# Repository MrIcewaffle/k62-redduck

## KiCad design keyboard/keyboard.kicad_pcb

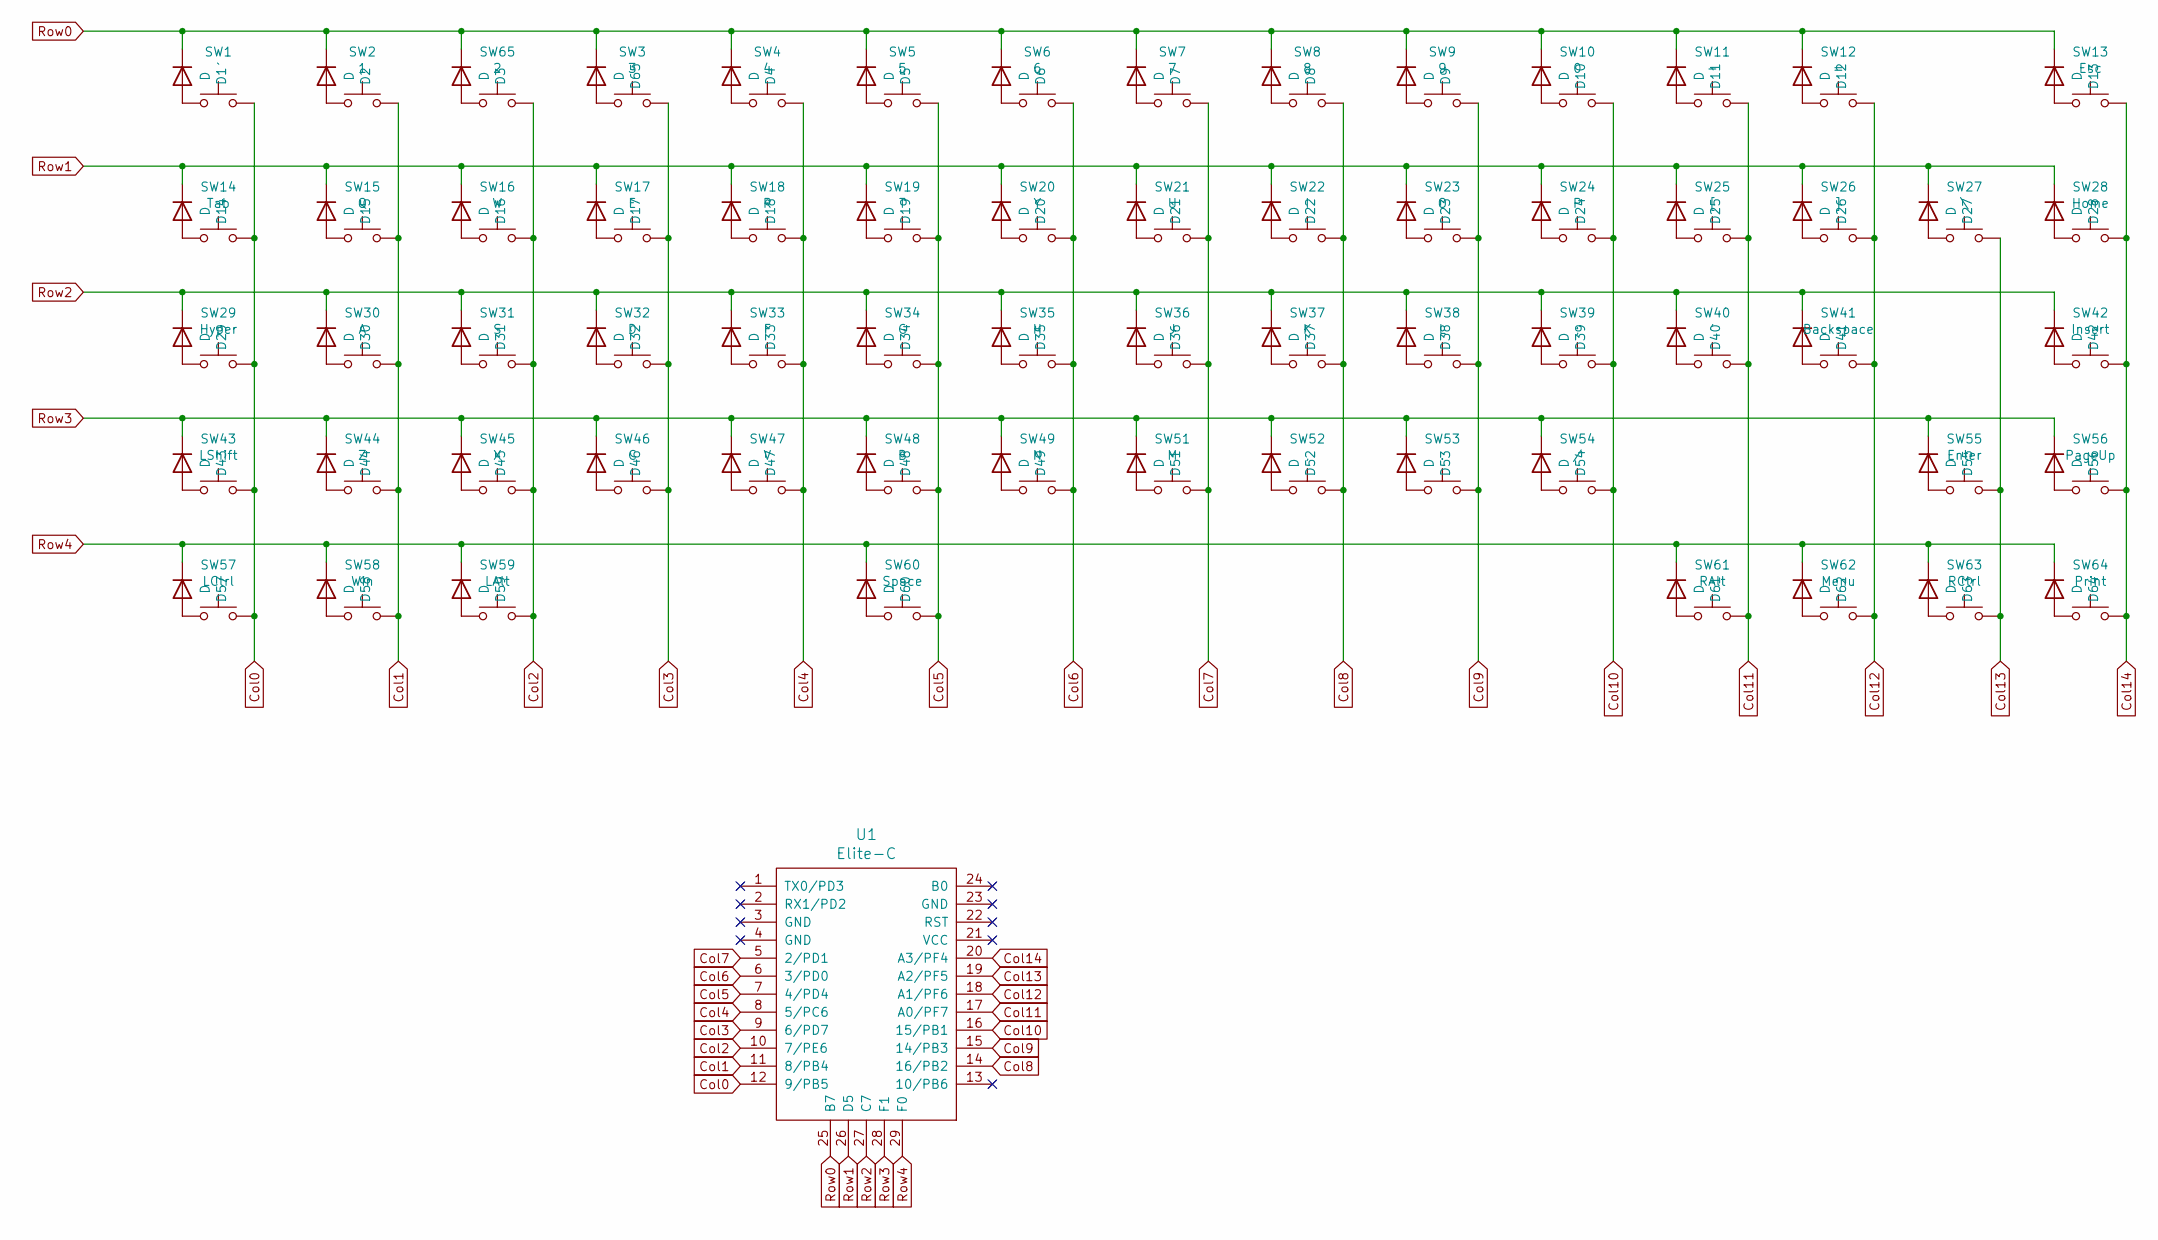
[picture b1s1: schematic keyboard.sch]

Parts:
D1, D2, D3, D4, D5, D6, D7, D8, D9, D10, D11, D12, D13, D14, D15, D16, D17, D18, D19, D20, D21, D22, D23, D24, D25, D26, D27, D28, D29, D30, D31, D32, D33, D34, D35, D36, D37, D38, D39, D40, D41, D42, D43, D44, D45, D46, D47, D48, D49, D51, D52, D53, D54, D55, D56, D57, D58, D59, D60, D61, D62, D63, D64, D65: D; D_0805
SW1: `; MX-Alps-Choc-1U-NoLED
SW2: 1; MX-Alps-Choc-1U-NoLED
SW3: 3; MX-Alps-Choc-1U-NoLED
SW4: 4; MX-Alps-Choc-1U-NoLED
SW5: 5; MX-Alps-Choc-1U-NoLED
SW6: 6; MX-Alps-Choc-1U-NoLED
SW7: 7; MX-Alps-Choc-1U-NoLED
SW8: 8; MX-Alps-Choc-1U-NoLED
SW9: 9; MX-Alps-Choc-1U-NoLED
SW10: 0; MX-Alps-Choc-1U-NoLED
SW11: -; MX-Alps-Choc-1U-NoLED
SW12: =; MX-Alps-Choc-1U-NoLED
SW13: Esc; MX-Alps-Choc-1U-NoLED
SW14: Tab; MX-Alps-Choc-1U-NoLED
SW15: Q; MX-Alps-Choc-1U-NoLED
SW16: W; MX-Alps-Choc-1U-NoLED
SW17: E; MX-Alps-Choc-1U-NoLED
SW18: R; MX-Alps-Choc-1U-NoLED
SW19: T; MX-Alps-Choc-1U-NoLED
SW20: Y; MX-Alps-Choc-1U-NoLED
SW21: U; MX-Alps-Choc-1U-NoLED
SW22: I; MX-Alps-Choc-1U-NoLED
SW23: O; MX-Alps-Choc-1U-NoLED
SW24: P; MX-Alps-Choc-1U-NoLED
SW25: [; MX-Alps-Choc-1U-NoLED
SW26: ]; MX-Alps-Choc-1U-NoLED
SW27: \\; MX-Alps-Choc-1U-NoLED
SW28: Home; MX-Alps-Choc-1U-NoLED
SW29: Hyper; MX-Alps-Choc-1U-NoLED
SW30: A; MX-Alps-Choc-1U-NoLED
SW31: S; MX-Alps-Choc-1U-NoLED
SW32: D; MX-Alps-Choc-1U-NoLED
SW33: F; MX-Alps-Choc-1U-NoLED
SW34: G; MX-Alps-Choc-1U-NoLED
SW35: H; MX-Alps-Choc-1U-NoLED
SW36: J; MX-Alps-Choc-1U-NoLED
SW37: K; MX-Alps-Choc-1U-NoLED
SW38: L; MX-Alps-Choc-1U-NoLED
SW39: ;; MX-Alps-Choc-1U-NoLED
SW40: '; MX-Alps-Choc-1U-NoLED
SW41: Backspace; MX-Alps-Choc-1U-NoLED
SW42: Insert; MX-Alps-Choc-1U-NoLED
SW43: LShift; MX-Alps-Choc-1U-NoLED
SW44: Z; MX-Alps-Choc-1U-NoLED
SW45: X; MX-Alps-Choc-1U-NoLED
SW46: C; MX-Alps-Choc-1U-NoLED
SW47: V; MX-Alps-Choc-1U-NoLED
SW48: B; MX-Alps-Choc-1U-NoLED
SW49: N; MX-Alps-Choc-1U-NoLED
SW51: M; MX-Alps-Choc-1U-NoLED
SW52: ,; MX-Alps-Choc-1U-NoLED
SW53: .; MX-Alps-Choc-1U-NoLED
SW54: /; MX-Alps-Choc-1U-NoLED
SW55: Enter; MX-Alps-Choc-1U-NoLED
SW56: PageUp; MX-Alps-Choc-1U-NoLED
SW57: LCtrl; MX-Alps-Choc-1U-NoLED
SW58: Win; MX-Alps-Choc-1U-NoLED
SW59: LAlt; MX-Alps-Choc-1U-NoLED
SW60: Space; MX-Alps-Choc-1U-NoLED
SW61: RAlt; MX-Alps-Choc-1U-NoLED
SW62: Menu; MX-Alps-Choc-1U-NoLED
SW63: RCtrl; MX-Alps-Choc-1U-NoLED
SW64: Print; MX-Alps-Choc-1U-NoLED
SW65: 2; MX-Alps-Choc-1U-NoLED
U1: Elite-C; Elite-C-castellated-29pin-holes

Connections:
Col0: SW1.2, SW14.2, SW29.2, SW43.2, SW57.2, U1.12 (9/PB5)
Col1: SW2.2, SW15.2, SW30.2, SW44.2, SW58.2, U1.11 (8/PB4)
Col2: SW16.2, SW31.2, SW45.2, SW59.2, SW65.2, U1.10 (7/PE6)
Col3: SW3.2, SW17.2, SW32.2, SW46.2, U1.9 (6/PD7)
Col4: SW4.2, SW18.2, SW33.2, SW47.2, U1.8 (5/PC6)
Col5: SW5.2, SW19.2, SW34.2, SW48.2, SW60.2, U1.7 (4/PD4)
Col6: SW6.2, SW20.2, SW35.2, SW49.2, U1.6 (3/PD0)
Col7: SW7.2, SW21.2, SW36.2, SW51.2, U1.5 (2/PD1)
Col8: SW8.2, SW22.2, SW37.2, SW52.2, U1.14 (16/PB2)
Col9: SW9.2, SW23.2, SW38.2, SW53.2, U1.15 (14/PB3)
Col10: SW10.2, SW24.2, SW39.2, SW54.2, U1.16 (15/PB1)
Col11: SW11.2, SW25.2, SW40.2, SW61.2, U1.17 (A0/PF7)
Col12: SW12.2, SW26.2, SW41.2, SW62.2, U1.18 (A1/PF6)
Col13: SW27.2, SW55.2, SW63.2, U1.19 (A2/PF5)
Col14: SW13.2, SW28.2, SW42.2, SW56.2, SW64.2, U1.20 (A3/PF4)
unnamed: D1.2 (A), SW1.1
unnamed: D2.2 (A), SW2.1
unnamed: D3.2 (A), SW65.1
unnamed: D4.2 (A), SW4.1
unnamed: D5.2 (A), SW5.1
unnamed: D6.2 (A), SW6.1
unnamed: D7.2 (A), SW7.1
unnamed: D8.2 (A), SW8.1
unnamed: D9.2 (A), SW9.1
unnamed: D10.2 (A), SW10.1
unnamed: D11.2 (A), SW11.1
unnamed: D12.2 (A), SW12.1
unnamed: D13.2 (A), SW13.1
unnamed: D14.2 (A), SW14.1
unnamed: D15.2 (A), SW15.1
unnamed: D16.2 (A), SW16.1
unnamed: D17.2 (A), SW17.1
unnamed: D18.2 (A), SW18.1
unnamed: D19.2 (A), SW19.1
unnamed: D20.2 (A), SW20.1
unnamed: D21.2 (A), SW21.1
unnamed: D22.2 (A), SW22.1
unnamed: D23.2 (A), SW23.1
unnamed: D24.2 (A), SW24.1
unnamed: D25.2 (A), SW25.1
unnamed: D26.2 (A), SW26.1
unnamed: D27.2 (A), SW27.1
unnamed: D28.2 (A), SW28.1
unnamed: D29.2 (A), SW29.1
unnamed: D30.2 (A), SW30.1
unnamed: D31.2 (A), SW31.1
unnamed: D32.2 (A), SW32.1
unnamed: D33.2 (A), SW33.1
unnamed: D34.2 (A), SW34.1
unnamed: D35.2 (A), SW35.1
unnamed: D36.2 (A), SW36.1
unnamed: D37.2 (A), SW37.1
unnamed: D38.2 (A), SW38.1
unnamed: D39.2 (A), SW39.1
unnamed: D40.2 (A), SW40.1
unnamed: D41.2 (A), SW41.1
unnamed: D42.2 (A), SW42.1
unnamed: D43.2 (A), SW43.1
unnamed: D44.2 (A), SW44.1
unnamed: D45.2 (A), SW45.1
unnamed: D46.2 (A), SW46.1
unnamed: D47.2 (A), SW47.1
unnamed: D48.2 (A), SW48.1
unnamed: D49.2 (A), SW49.1
unnamed: D51.2 (A), SW51.1
unnamed: D52.2 (A), SW52.1
unnamed: D53.2 (A), SW53.1
unnamed: D54.2 (A), SW54.1
unnamed: D55.2 (A), SW55.1
unnamed: D56.2 (A), SW56.1
unnamed: D57.2 (A), SW57.1
unnamed: D58.2 (A), SW58.1
unnamed: D59.2 (A), SW59.1
unnamed: D60.2 (A), SW60.1
unnamed: D61.2 (A), SW61.1
unnamed: D62.2 (A), SW62.1
unnamed: D63.2 (A), SW63.1
unnamed: D64.2 (A), SW64.1
unnamed: D65.2 (A), SW3.1
Row0: D1.1 (K), D2.1 (K), D3.1 (K), D4.1 (K), D5.1 (K), D6.1 (K), D7.1 (K), D8.1 (K), D9.1 (K), D10.1 (K), D11.1 (K), D12.1 (K), D13.1 (K), D65.1 (K), U1.25 (B7)
Row1: D14.1 (K), D15.1 (K), D16.1 (K), D17.1 (K), D18.1 (K), D19.1 (K), D20.1 (K), D21.1 (K), D22.1 (K), D23.1 (K), D24.1 (K), D25.1 (K), D26.1 (K), D27.1 (K), D28.1 (K), U1.26 (D5)
Row2: D29.1 (K), D30.1 (K), D31.1 (K), D32.1 (K), D33.1 (K), D34.1 (K), D35.1 (K), D36.1 (K), D37.1 (K), D38.1 (K), D39.1 (K), D40.1 (K), D41.1 (K), D42.1 (K), U1.27 (C7)
Row3: D43.1 (K), D44.1 (K), D45.1 (K), D46.1 (K), D47.1 (K), D48.1 (K), D49.1 (K), D51.1 (K), D52.1 (K), D53.1 (K), D54.1 (K), D55.1 (K), D56.1 (K), U1.28 (F1)
Row4: D57.1 (K), D58.1 (K), D59.1 (K), D60.1 (K), D61.1 (K), D62.1 (K), D63.1 (K), D64.1 (K), U1.29 (F0)

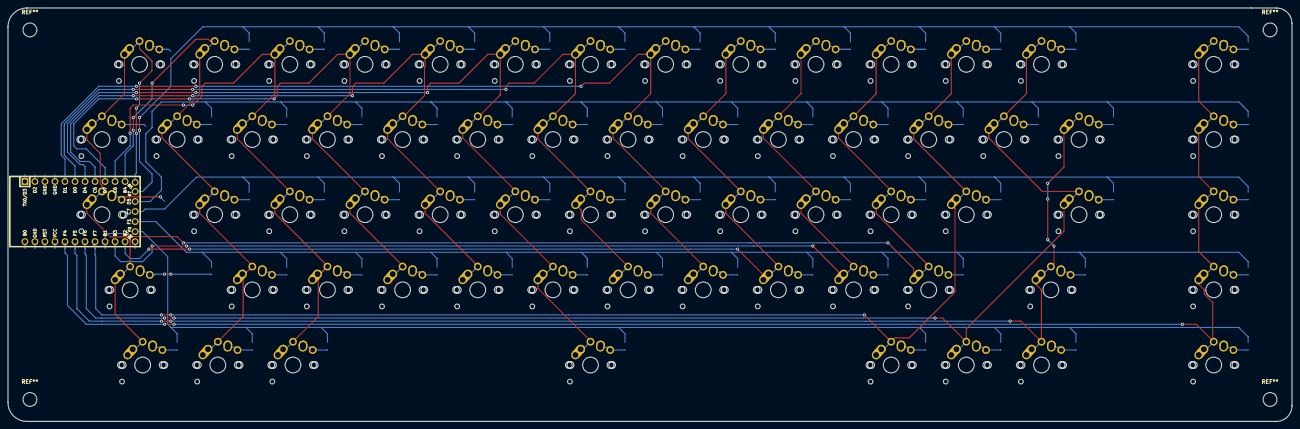
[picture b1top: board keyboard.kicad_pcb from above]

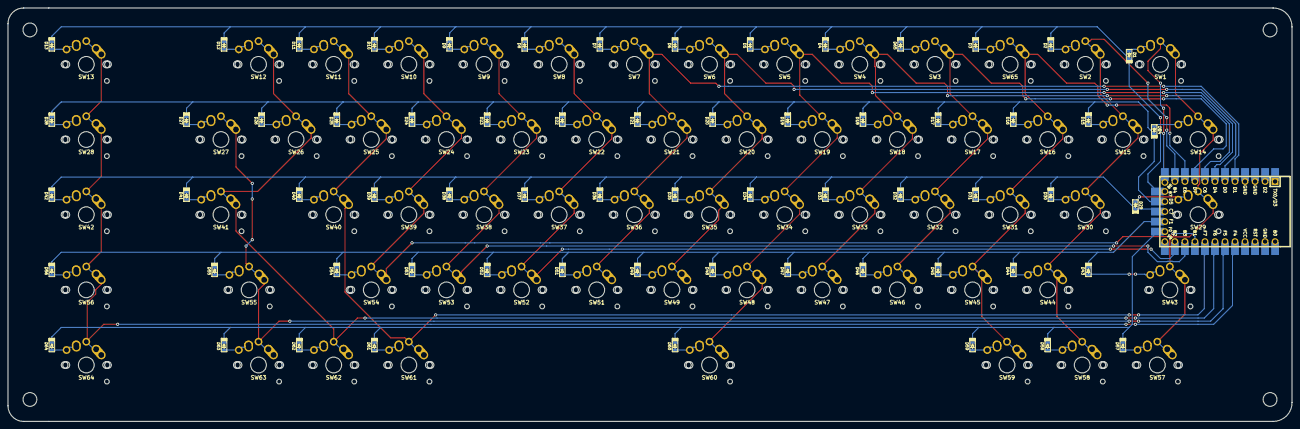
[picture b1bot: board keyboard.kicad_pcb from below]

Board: 2 copper layers, 325.4 x 104.8 mm, 129 parts (65 on the bottom side), 84 nets.

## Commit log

2021-11-12 ref+sch+pcb
2021-11-25 completed pcb layout
